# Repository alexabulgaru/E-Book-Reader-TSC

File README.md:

# E-Book-Reader-TSC - Bulgaru Alexandra 331CD

## Diagrama bloc

## Bill Of Materials (BOM)
| Componenta | Achizitie | Datasheet |
| ---------- | --------- | --------- |
| PFMF.050.1 | [Cumpara](https://ro.mouser.com/ProductDetail/Schurter/PFMF.050.2?qs=1auRipcfynCums5v1iucSA%3D%3D) |  [Datasheet](https://ro.mouser.com/datasheet/2/358/typ_PFMF-1275918.pdf) |
| USB4110-GF-A | [Cumpara](https://ro.mouser.com/ProductDetail/GCT/USB4110-GF-A?qs=KUoIvG%2F9IlYiZvIXQjyJeA%3D%3D) | [Datasheet](https://ro.mouser.com/datasheet/2/837/GCT_USB4110_Product_Drawing___20k_cycles-3455479.pdf) |
| USBLC6-2SC6Y | [Cumpara](https://ro.mouser.com/ProductDetail/STMicroelectronics/USBLC6-2SC6Y?qs=gNDSiZmRJS%2FOgDexvXkdow%3D%3D) | [Datasheet](https://ro.mouser.com/datasheet/2/389/usblc6_2sc6y-1852505.pdf) |
| SD0805S020S1R0 | [Cumpara](https://ro.mouser.com/ProductDetail/KYOCERA-AVX/SD0805S020S1R0?qs=jCA%252BPfw4LHbpkAoSnwrdjw%3D%3D) | [Datasheet](https://ro.mouser.com/datasheet/2/40/schottky-3165252.pdf) |
| DMG2305UX-7 | [Cumpara](https://ro.mouser.com/ProductDetail/Diodes-Incorporated/DMG2305UX-7?qs=L1DZKBg7t5F%2FNBHrjfxC%252Bg%3D%3D) | [Datasheet](https://www.diodes.com/assets/Datasheets/DMG2305UX.pdf) |
| XC6220A331MR-G | [Cumpara](https://ro.mouser.com/ProductDetail/Torex-Semiconductor/XC6220A331MR-G?qs=AsjdqWjXhJ8ZSWznL1J0gg%3D%3D) | [Datasheet](https://ro.mouser.com/datasheet/2/760/xc6220-3371556.pdf) |
| Condensator 100 uF TANT | [Cumpara](https://ro.mouser.com/ProductDetail/KYOCERA-AVX/TAJW107M010RNJ?qs=Wtp%252Bf%2FAeVqIH8v1VxV%252B1Rg%3D%3D) | [Datasheet](https://ro.mouser.com/datasheet/2/40/TAJ-3165264.pdf) |
| 112A-TAAR-R03_ATTEND | [Cumpara](https://www.digikey.ro/en/products/detail/attend-technology/112A-TAAR-R03/17633923) | [Datasheet](https://www.attend.com.tw/data/download/file/112A-TAAR-R03_Spec.pdf)
| ESP32-C6-WROOM-1-N8 | [Cumpara](https://ro.mouser.com/ProductDetail/Espressif-Systems/ESP32-C6-WROOM-1-N8?qs=8Wlm6%252BaMh8ST02Gmwp74cw%3D%3D) | [Datasheet](https://ro.mouser.com/datasheet/2/891/Espressif_ESP32_C6_WROOM_1__Datasheet_V0_1_PRELIMI-3239987.pdf) |
| MCP73831 | [Cumpara](https://ro.mouser.com/ProductDetail/Microchip-Technology/MCP73831T-2ACI-OT?qs=yUQqVecv4qvbBQBGbHx0Mw%3D%3D) | [Datasheet](https://ro.mouser.com/datasheet/2/268/MCP73831_Family_Data_Sheet_DS20001984H-3441711.pdf) |
| CHG_LED | [Cumpara](https://store.comet.srl.ro/Catalogue/Product/40478/) | [Datasheet](https://www.snapeda.com/parts/KP-1608SURCK/Kingbright/datasheet/) |
| SI1308EDL-T1-GE3 | [Cumpara](https://ro.mouser.com/ProductDetail/Vishay-Semiconductors/SI1308EDL-T1-GE3?qs=bX1%252BNvsK%2FBramh9tgpOaEw%3D%3D) | [Datasheet](https://www.vishay.com/doc?63399) |
| MBR0530 | [Cumpara](https://ro.mouser.com/ProductDetail/Micro-Commercial-Components-MCC/MBR0530-T?qs=9VyI4qLX4NTSXkb9ynzJnA%3D%3D) | [Datasheet](https://ro.mouser.com/datasheet/2/258/mcc_mbr0520~mbr0560sod123-1179695.pdf) |
| Bobina | [Cumpara](https://ro.mouser.com/ProductDetail/Wurth-Elektronik/744043680?qs=PGXP4M47uW6VkZq%252BkzjrHA%3D%3D) | [Datasheet](https://www.we-online.com/components/products/datasheet/744043680.pdf) |
| FH34SRJ-24S-0.5SH_99_ | [Cumpara](https://ro.mouser.com/ProductDetail/Hirose-Connector/FH34SRJ-24S-0.5SH99?qs=vcbW%252B4%252BSTIpKBl5ap9J8Fw%3D%3D) | [Datasheet](https://ro.mouser.com/datasheet/2/185/FH34SRJ_24S_0_5SH_99__CL0580_1255_6_99_2DDrawing_0-1615044.pdf) |
| BME688 | [Cumpara](https://ro.mouser.com/ProductDetail/Bosch-Sensortec/BME688?qs=IS%252B4QmGtzzqQoVDscqwx3A%3D%3D) | [Datasheet](https://ro.mouser.com/datasheet/2/783/bst_bme688_fl000-2307034.pdf) |
| BD5229G-TR | [Cumpara](https://ro.mouser.com/ProductDetail/ROHM-Semiconductor/BD5229G-TR?qs=4kLU8WoGk0vvnhrrYwdszw%3D%3D) | [Datasheet](https://fscdn.rohm.com/en/products/databook/datasheet/ic/power/voltage_detector/bd52xxg-e.pdf) |
| Buton adaptat | [Cumpara](https://ro.mouser.com/ProductDetail/CK/KMR221GULCLFS?qs=u2NJ%252B70r0goBXaNk7IrU0Q%3D%3D) | [Datasheet](https://www.ckswitches.com/media/1479/kmr2.pdf) |
| MAX17048G+T10 | [Cumpara](https://ro.mouser.com/ProductDetail/Analog-Devices-Maxim-Integrated/MAX17048G%2bT10?qs=D7PJwyCwLAoGnnn8jEPRBQ%3D%3D) | [Datasheet](https://ro.mouser.com/datasheet/2/609/MAX17048_MAX17049-3469099.pdf) |
| W25Q512JVEIQ | [Cumpara](https://ro.mouser.com/ProductDetail/Winbond/W25Q512JVEIQ?qs=l7cgNqFNU1jw6svr3at6tA%3D%3D) | [Datasheet](https://ro.mouser.com/datasheet/2/949/Winbond_W25Q512JV_Datasheet-3240039.pdf) |
| PGB1010603MR | [Cumpara](https://ro.mouser.com/ProductDetail/Littelfuse/PGB1010603MRHF?qs=KvZd0dN2Zg%2FuIq6icj%252BGKA%3D%3D) | [Datasheet](https://www.littelfuse.com/media?resourcetype=datasheets&itemid=8a337998-d54d-466b-be4e-dc5bcd1f9321&filename=littelfuse_pulseguard_pgb1_datasheet.pdf) |
| QWIIC_RIGHT_ANGLE | [Cumpara](https://ro.mouser.com/ProductDetail/GCT/USB4110-GF-A?qs=KUoIvG%2F9IlYiZvIXQjyJeA%3D%3D) | [Datasheet](https://ro.mouser.com/datasheet/2/837/GCT_USB4110_Product_Drawing___20k_cycles-3455479.pdf) |
| DS3231SN# | [Cumpara](https://ro.mouser.com/ProductDetail/Analog-Devices-Maxim-Integrated/DS3231SN?qs=ffX8NcjNb2RmKAb9wAk9Ug%3D%3D) | [Datasheet](https://ro.mouser.com/datasheet/2/609/DS3231-3421123.pdf) |
| CPH3225A C10_SUPERCAP | [Cumpara](https://ro.mouser.com/ProductDetail/Seiko-Semiconductors/CPH3225A?qs=3etwrb1wR%252BhUOph6lAO7eg%3D%3D) | [Datasheet](https://ro.mouser.com/datasheet/2/360/Seiko_Instruments_MicroBattery_E_20230330_2024Jan_-3561061.pdf) |
| Condensator 100nF | [Cumpara](https://ro.mouser.com/ProductDetail/KYOCERA-AVX/06033G104ZAT2A?qs=NXubJDmysXJMPmHfVo6Z%252BA%3D%3D) | [Datasheet](https://ro.mouser.com/datasheet/2/40/KGM_Y5V-3223189.pdf) |
| Condensator 4.7uF | [Cumpara](https://ro.mouser.com/ProductDetail/KYOCERA-AVX/0402ZD475MAT2A?qs=NBFAU1oqP4W4U2PCPHI0sg%3D%3D) | [Datasheet](https://ro.mouser.com/datasheet/2/40/cx5r_KGM-3223198.pdf) |
| Condensator 10uF | [Cumpara](https://ro.mouser.com/ProductDetail/Samsung-Electro-Mechanics/CL10A106KQ8NNNL?qs=xZ%2FP%252Ba9zWqaes9JKSsob2Q%3D%3D) | [Datasheet](https://ro.mouser.com/datasheet/2/585/MLCC-1837944.pdf) |
| Condensator 1uF/50V | [Cumpara](https://ro.mouser.com/ProductDetail/KYOCERA-AVX/06035D105MAT2A?qs=k4kUdCzLgS5%252BURKe1SOIeQ%3D%3D) | [Datasheet](https://ro.mouser.com/datasheet/2/40/cx5r_KGM-3223198.pdf) |
| Rezistenta 10K | [Cumpara](https://ro.mouser.com/ProductDetail/Vishay-Beyschlag/MCS0402MD1002BE000?qs=17u8i%2FzlE8%2F9BrAaXkMk1w%3D%3D) | [Datasheet](https://www.vishay.com/doc?28952) |
| Rezistenta 200 | [Cumpara](https://ro.mouser.com/ProductDetail/Vishay-Beyschlag/MCS0402MD2000BE100?qs=3SvaY9RawMJNVte4F12%252BZQ%3D%3D) | [Datasheet](https://www.vishay.com/doc?28952) |
| Rezistenta 100K | [Cumpara](https://ro.mouser.com/ProductDetail/Vishay-Beyschlag/MCT0603PD1003DP500?qs=5aG0NVq1C4wWAn8Ei3OpZA%3D%3D) | [Datasheet](https://www.vishay.com/doc?28916) |
| Rezistenta 2.2 | [Cumpara](https://ro.mouser.com/ProductDetail/SEI-Stackpole/RMCF0402FT2R20?qs=IPgv5n7u5QbBgyl0jwhwsA%3D%3D) | [Datasheet](https://ro.mouser.com/datasheet/2/385/SEI_RMCF_RMCP-3077565.pdf) |
| Rezistenta 5K1| [Cumpara](https://www.venkel.com/part/TFCR0603-16W-K-5690FT) | [Datasheet](https://data.venkel.com/documents/tfcr-series?_gl=1*tdo8m*_ga*NTA1MTc5MTcyLjE3NDM4OTMzNjc.*_ga_JRKGBZNVM8*MTc0Mzg5MzM2Ni4xLjAuMTc0Mzg5MzM2OC41OC4wLjA.) |
| Rezistenta 2K | [Cumpara](https://ro.mouser.com/ProductDetail/Vishay-Beyschlag/MCS04020C2001FE000?qs=wTZ%2FFzl837YG0wIkZJJOwQ%3D%3D) | [Datasheet](https://www.vishay.com/doc?28705) |
| Rezistenta 0.47 | [Cumpara](https://ro.mouser.com/ProductDetail/SEI-Stackpole/CSR0402JKR470?qs=IPgv5n7u5QawIB6nBEt8wA%3D%3D) | [Datasheet](https://ro.mouser.com/datasheet/2/385/SEI_CSR_CSRN-3077593.pdf) |
| Rezistenta 15 | [Cumpara](https://ro.mouser.com/ProductDetail/YAGEO/RT0402FRE0715RL?qs=BXCcY9r%252B08DFFpLSkPOIqQ%3D%3D) | [Datasheet](https://ro.mouser.com/datasheet/2/447/PYu_RT_1_to_0_01_RoHS_L_15-3461507.pdf) |
| SJ | [Cumpara](https://grabcad.com/library/solder-jumpers-1) | [Datasheet](https://docs.rs-online.com/6fae/A700000010766261.pdf)

## Functionalitatea Hardware
#### Alimentare & Baterie:
USB-C furnizeaza 5 V, intra in controllerul de incarcare Li-Po si LDO-ul de 3.3 V. Acest 3.3 V alimenteaza microcontrolerul (ESP32-C6), senzorii si perifericele. Bateria Li-Po asigura functionarea cand nu este disponibila o sursa USB.

Microcontrolerul (ESP32-C6) ruleaza firmware-ul, se conecteaza la retea (Wi-Fi 6, BLE), citeste senzorii interni (BME688, DS3231) si scrie/afiseaza pe ecranul E-Paper. Poate salva date sau citi fisiere din memoria externa Flash NOR sau de pe cardul SD.

#### Senzori & RTC:
BME688 (temperatura, umiditate, presiune, compusi volatili) si DS3231 (timp real) sunt pe magistrala I2C, astfel incat datele sunt preluate usor si prelucrate.

#### Afisaj E-Paper:
Se actualizeaza prin magistrala SPI; microcontrolerul trimite datele necesare prin pinul EPD_CS (chip select), EPD_DC (command/data), EPD_RST, iar afisajul confirma starea prin EPD_BUSY.

#### Extensii:
Qwiic / Stemma QT ofera posibilitatea de a conecta senzori suplimentari pe magistrala I2C; exista si un slot SD.

## Pini ESP32-C6
| Nume      | GPIO / Pin       | Functie                                         | Descriere                                                                                                                    |
|-----------------|------------------|-------------------------------------------------|------------------------------------------------------------------------------------------------------------------------------|
| **3V3**         | 3V3             | Sursa principala de 3.3V                        | Asigura alimentarea necesara functionarii ESP32-C6 si a componentelor logice de pe placa                                     |
| **EN (Reset)**  | EN              | Activare/Dezactivare microcontroler             | Controleaza alimentarea interna a modulului ESP32-C6; un impuls LOW poate reseta intregul sistem                             |
| **USB_D-**      | IO12            | Linia negativa pentru USB                       | Utilizata in transferul de date prin protocol USB 2.0, in pereche diferentiala cu USB_D+                                     |
| **USB_D+**      | IO13            | Linia pozitiva pentru USB                       | Utilizata in transferul de date prin protocol USB 2.0, in pereche diferentiala cu USB_D-                                     |
| **Buton Boot**  | IO9             | Intrare in modul bootloader                     | Se conecteaza la masa pentru a forta incarcarea bootloader-ului ESP32-C6 (flash/programare firmware)                         |
| **Buton Change**| IO15            | Comutare mod de operare                         | Poate fi configurat in firmware pentru a schimba starea aplicatiei sau diverse moduri de functionare                        |
| **TX (UART)**   | TXD0 / GPIO16   | Emisie seriala (UART)                           | Trimite date catre un terminal serial sau adaptor USB-serial, folosit pentru debug sau comunicatie                          |
| **RX (UART)**   | RXD0 / GPIO17   | Receptie seriala (UART)                         | Primeste date de la un terminal serial sau adaptor USB-serial, folosit pentru debug sau comunicatie                         |
| **SCK (SPI)**   | IO6             | Ceas SPI pentru transfer de date                | Genereaza impulsurile de sincronizare pentru toate dispozitivele conectate la magistrala SPI                                 |
| **MOSI (SPI)**  | IO7             | Linie de date catre dispozitive SPI (Master Out)| Transmite informatii de la microcontroler catre NOR Flash, card SD si ecran E-Paper                                          |
| **MISO (SPI)**  | IO2             | Linie de date de la dispozitive SPI (Master In) | Receptioneaza informatii de la card SD, E-Paper si alte periferice SPI                                                      |
| **FLASH_CS**    | IO11            | Selectare chip pentru memoria NOR Flash         | Activeaza NOR Flash atunci cand se lucreaza cu acesta pe magistrala SPI                                                      |
| **EPD_CS**      | IO10            | Selectare chip pentru E-Paper                   | Activeaza modulul E-Paper pe magistrala SPI in timpul transferului de date                                                  |
| **EPD_DC**      | IO5             | Diferentiere comanda/date pentru E-Paper        | Indica daca informatia transmisa pe SPI reprezinta instructiuni de control sau date de afisare                              |
| **EPD_RST**     | IO23            | Reset extern E-Paper                            | Permite repornirea hardware a modulului E-Paper in cazul in care este necesar                                               |
| **EPD_BUSY**    | IO3             | Semnal de ocupare E-Paper                       | Avertizeaza microcontrolerul ca E-Paper este in curs de actualizare si nu poate primi alte comenzi                          |
| **SDA (I2C)**   | IO21            | Linie de date I2C                               | Utilizata pentru comunicatia bidirectionala cu RTC DS3231, senzor BME688 si conector Qwiic/Stemma QT                        |
| **SCL (I2C)**   | IO22            | Linie de ceas I2C                               | Sincronizeaza toate transferurile de pe magistrala I2C, inclusiv cu RTC, senzori si module de extensie                     |
| **SS_SD**       | IO4             | Chip Select pentru card SD (SPI)               | Stabileste cand cardul SD este activ pe magistrala SPI, prevenind conflicte cu alte dispozitive                            |
| **I2C_PW**      | IO19            | Control alimentare senzori I2C                 | Poate porni sau opri tensiunea pentru senzorii conectati la magistrala I2C, contribuind la economisirea energiei           |
| **EPD_3V3_C**   | IO20            | Alimentare 3.3V dedicata E-Paper               | Linie separata de 3.3V pentru a alimenta in mod specific modulul E-Paper si pentru a asigura stabilitatea semnalelor       |
| **32KHZ**       | IO1             | Linie semnal 32 kHz                            | Frecventa de ceas folosita de modulul RTC sau alte circuite care necesita un clock de 32 kHz                                |
| **INT_RTC**     | IO0             | Intrerupere de la RTC DS3231                   | Poate trezi ESP32-C6 din mod sleep sau poate semnala evenimente programate in RTC                                           |
| **RTC_RST**     | IO18            | Reset extern RTC                                | Linie pentru resetarea manuala a ceasului de timp real in situatii speciale                                                |

## Estimare consum

| Componenta       | Consum Activ (aprox) | Consum Sleep (aprox) | Observatii                                                                              |
|------------------|-----------------------|-----------------------|-----------------------------------------------------------------------------------------|
| ESP32-C6         | ~80–100 mA (Wi-Fi)   | ~10–20 µA (DeepSleep)| Principalul consumator; Wi-Fi creste semnificativ consumul in mod activ                 |
| Senzor BME688    | ~2 mA in masurare    | <1 µA in standby     | Majoritatea timpului poate fi oprit sau in standby                                     |
| RTC DS3231       | ~150–200 µA          | ~3 µA in mod backup  | Funcioneaza permanent, dar consuma relativ putin                                        |
| NOR Flash (SPI)  | ~10–30 mA            | ~1 µA (Deep PwrDown) | Activ doar la operatiile de citire/scriere                                             |
| E-Paper Display  | ~20–50 mA la refresh | ~0 µA in pasiv       | Odata afisat, nu mai consuma energie pentru mentinerea imaginii                        |
| LDO + pasive     | ~10–50 µA            | n/a                  | Curent de repaus al regulatorului si mici consumuri auxiliare (rezistente, LED-uri etc.) |

## Etape implementare
1. Schematic: Am creat schematicul pe baza schemei electrice furnizate. Am folosit biblioteca DeskAssitant si am rulat ERC pentru a verifica prezenta erorilor.

2. PCB:
- Din schematic am dat "switch to PCB" si am plasat componentele conform modelului. Am desenat placa potrivit dimensiunilor, adaugand si decuparile. Componentele principale erau destul de vizibile, condensatoarele si rezistenele le-am asezat in functie de proximitatea acestora din schematic fata de componentele mari.
-Am facut autorutare pe top si pe bottom cu 0.15 mm, apoi am modificat grosimile firelor de alimentare sa fie minim 0.30 mm.
- Am creat planurile de masa cu semnalul GND, ulterior adaugand si via stitching tot cu semnalul GND. Majoritatea via stitching-urilor le-am pozitionat in jurul antenei.

3. 3D: Am adaugat in schematic componentele 3D din [Component Search Engine](https://componentsearchengine.com). Le-am pozitionat apoi conform footprint-ului.

4. Update carcasa: Dupa ce am pozitionat placuta in carcasa, am modificat carcasa astfel incat sa se potriveasca mufele.

5. Am creat modelele 3D pentru carcasa si display conform schemelor si le-am asezat in carcasa.

## Erori/probleme intampinate
1. Am acceptat erorile de PCB de tipul SMD-Hole Board.

2. Am uitat sa verific schematicul cu ERC prima data si am rulat abia dupa ce am terminat de importat toate componentele 3D. Am observat o eroare, a trebuit sa refac o conexiune si am reluat procesul de rutare, planuri de masa si via stitching.

3. Am modificat butoanele sa se potriveasca pe footprint.

4. Cand am generat prima data placuta 3D, aveam o portiune din PCB incompleta pe care nu am vazut-o. Din acest motiv, placuta avea gauri. Am corectat si am facut iar planul de masa si via stitching.

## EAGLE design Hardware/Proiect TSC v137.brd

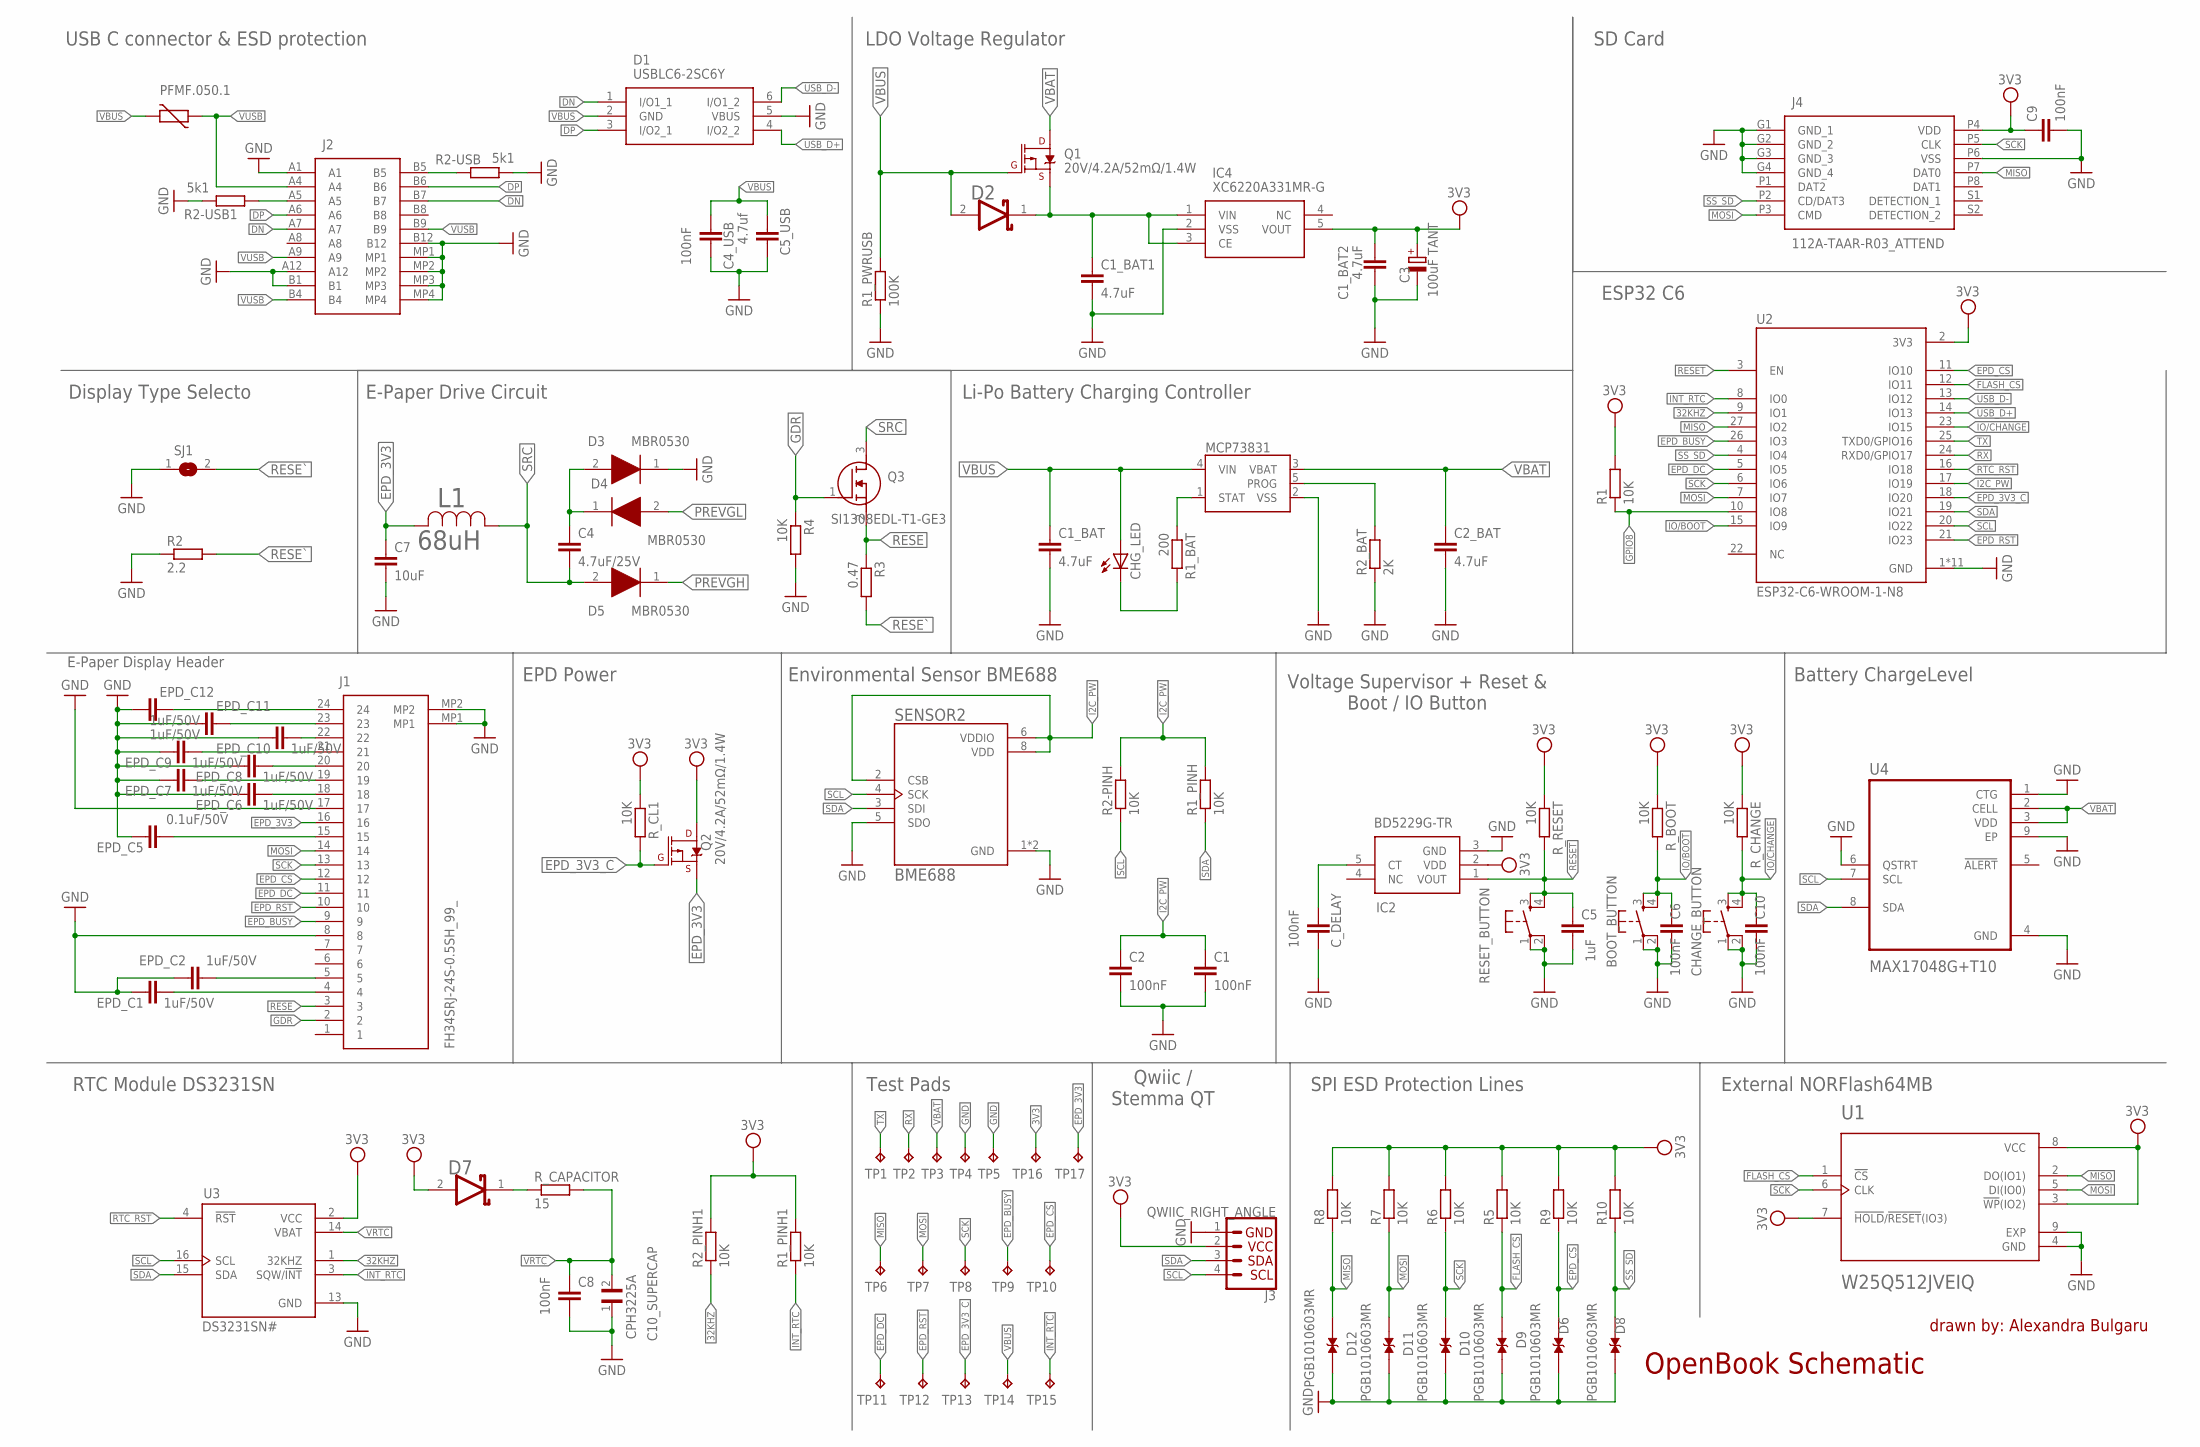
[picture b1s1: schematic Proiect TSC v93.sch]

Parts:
BOOT_BUTTON: BUTTON_CUSYOMV1; MYBUTTON
C1, C2, C4_USB, C6, C8, C10: 100nF; EAGLE-LTSPICE_C0402
C1_BAT, C1_BAT1, C1_BAT2, C2_BAT: 4.7uF; EAGLE-LTSPICE_C0402
C3: 100uF TANT; RCL_CT3528
C4: 4.7uF/25V; EAGLE-LTSPICE_C0402
C5: 1uF; EAGLE-LTSPICE_C0402
C5_USB: 4.7uf; EAGLE-LTSPICE_C0402
C7: 10uF; EAGLE-LTSPICE_C0402
C9: 100nF; ESP32_WROVER_EAGLE-LTSPICE_C0402
C10_SUPERCAP: CPH3225A; CAPCP3225X100N
CHANGE_BUTTON: BUTTON_CUSYOMV1; MYBUTTON
CHG_LED: ADAFRUIT_LEDCHIP-LED0603; ADAFRUIT_CHIP-LED0603
C_DELAY: 100nF; EAGLE-LTSPICE_C0402
D1: USBLC6-2SC6Y; SOT95P280X145-6N
D2, D7: ESP32_WROVER_AVX---SD0805S020S1R0_AVX_SD0805S020S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; ESP32_WROVER_AVX---SD0805S020S1R0_AVX_SD0805S020S1R0_0
D3, D4, D5: MBR0530; SOD3716X135N
D6, D8, D9, D10, D11, D12: PGB1010603MR; DIOC1608X36N
EPD_C1, EPD_C2, EPD_C6, EPD_C7, EPD_C8, EPD_C9, EPD_C10, EPD_C11, EPD_C12: 1uF/50V; EAGLE-LTSPICE_C0402
EPD_C5: 0.1uF/50V; EAGLE-LTSPICE_C0402
IC2: BD5229G-TR; SOT95P280X125-5N
IC4: XC6220A331MR-G; SOT95P280X120-5N
J1: FH34SRJ-24S-0.5SH_99_; FH34SRJ24S05SH99
J2: SAMACSYS_PARTS_USB4110-GF-A; SAMACSYS_PARTS_USB4110GFA
J3: QWIIC_RIGHT_ANGLE; JST04_1MM_RA
J4: 112A-TAAR-R03_ATTEND; 112ATAARR03ATTEND
L1: 68uH; IND_4828-WE-TPC_WRE
MCP73831: ESP32_WROVER_SPARKFUN-IC-POWER_MCP73831; ESP32_WROVER_SPARKFUN-IC-POWER_SOT23-5
PFMF.050.1: ESP32C6_VARISTORCN1812; ESP32C6_VARISTOR_CT/CN1812
Q1, Q2: 20V/4.2A/52mΩ/1.4W; ESP32_WROVER_SPARKFUN-DISCRETESEMI_SOT23-3
Q3: SI1308EDL-T1-GE3; SOT65P210X110-3N
R1, R1_PINH, R1_PINH1, R2-PINH, R2_PINH1, R4, R5, R6, R7, R8, R9, R10: 10K; ESP32_WROVER_EAGLE-LTSPICE_R0402
R1_BAT: 200; ESP32_WROVER_EAGLE-LTSPICE_R0402
R1_PWRUSB: 100K; ESP32_WROVER_EAGLE-LTSPICE_R0402
R2: 2.2; ESP32_WROVER_EAGLE-LTSPICE_R0402
R2-USB, R2-USB1: 5k1; ESP32_WROVER_EAGLE-LTSPICE_R0402
R2_BAT: 2K; ESP32_WROVER_EAGLE-LTSPICE_R0402
R3: 0.47; ESP32_WROVER_EAGLE-LTSPICE_R0402
RESET_BUTTON: BUTTON_CUSYOMV1; MYBUTTON
R_BOOT: 10K; ESP32_WROVER_EAGLE-LTSPICE_R0402
R_CAPACITOR: 15; ESP32_WROVER_EAGLE-LTSPICE_R0402
R_CHANGE: 10K; ESP32_WROVER_EAGLE-LTSPICE_R0402
R_CL1: 10K; ESP32_WROVER_EAGLE-LTSPICE_R0402
R_RESET: 10K; ESP32_WROVER_EAGLE-LTSPICE_R0402
SENSOR2: BME688; ESP32_WROVER_BME680_PSON80P300X300X100-8N
SJ1: SJ
TP1, TP2, TP3, TP4, TP5, TP6, TP7, TP8, TP9, TP10, TP11, TP12, TP13, TP14, TP15, TP16, TP17: TPTP20R; TP20R
U1: W25Q512JVEIQ; SON127P600X800X80-9N
U2: ESP32-C6-WROOM-1-N8; XCVR_ESP32-C6-WROOM-1-N8
U3: DS3231SN#; SOIC127P1032X265-16N
U4: MAX17048G+T10; SON50P200X200X80-9N

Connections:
3V3: C1_BAT2.2, C3.+, C9.1, D7.2 (ANODE), IC2.2 (VDD), IC4.5 (VOUT), J3.2, J4.P4 (VDD), Q2.3 (D), R1.2, R1_PINH1.2, R2_PINH1.2, R5.2, R6.2, R7.2, R8.2, R9.2, R10.2, R_BOOT.1, R_CHANGE.1, R_CL1.1, R_RESET.1, TP16.TP, U1.3 (!WP!(IO2)), U1.7 (!HOLD!/!RESET!(IO3)), U1.8 (VCC), U2.2 (3V3), U3.2 (VCC)
32KHZ: R2_PINH1.1, U2.9 (IO1), U3.1 (32KHZ)
DN: D1.1 (I/O1_1), J2.A7, J2.B7
DP: D1.3 (I/O2_1), J2.A6, J2.B6
EPD_3V3: C7.1, J1.16, L1.2, Q2.2 (S), TP17.TP
EPD_3V3_C: Q2.1 (G), R_CL1.2, TP13.TP, U2.18 (IO20)
EPD_BUSY: J1.9, TP9.TP, U2.26 (IO3)
EPD_CS: D6.1, J1.12, R9.1, TP10.TP, U2.11 (IO10)
EPD_DC: J1.11, TP11.TP, U2.5 (IO5)
EPD_RST: J1.10, TP12.TP, U2.21 (IO23)
FLASH_CS: D9.1, R5.1, U1.1 (!CS), U2.12 (IO11)
GDR: J1.2, Q3.1 (G), R4.1
GPIO8: R1.1, U2.10 (IO8)
I2C_PW: C1.1, C2.1, R1_PINH.2, R2-PINH.2, SENSOR2.2 (CSB), SENSOR2.6 (VDDIO), SENSOR2.8 (VDD), U2.17 (IO19)
INT_RTC: R1_PINH1.1, TP15.TP, U2.8 (IO0), U3.3 (SQW/!INT)
IO/BOOT: BOOT_BUTTON.3, BOOT_BUTTON.4, C6.1, R_BOOT.2, U2.15 (IO9)
IO/CHANGE: C10.1, CHANGE_BUTTON.3, CHANGE_BUTTON.4, R_CHANGE.2, U2.23 (IO15)
MISO: D12.1, J4.P7 (DAT0), R8.1, TP6.TP, U1.2 (DO(IO1)), U2.27 (IO2)
MOSI: D11.1, J1.14, J4.P3 (CMD), R7.1, TP7.TP, U1.5 (DI(IO0)), U2.7 (IO7)
unnamed: J2.B5, R2-USB.1
unnamed: J2.A5, R2-USB1.1
unnamed: C1_BAT1.1, D2.1 (CATHODE), IC4.1 (VIN), IC4.3 (CE), Q1.2 (S)
unnamed: MCP73831.1 (STAT), R1_BAT.1
unnamed: C4.1, D3.2 (A), D4.1 (K)
unnamed: CHG_LED.C, R1_BAT.2
unnamed: MCP73831.5 (PROG), R2_BAT.2
unnamed: EPD_C1.2, J1.4
unnamed: EPD_C2.2, J1.5
unnamed: EPD_C5.2, J1.15
unnamed: EPD_C6.2, J1.18
unnamed: EPD_C7.2, J1.19
unnamed: EPD_C8.2, J1.20
unnamed: EPD_C10.2, J1.22
unnamed: C_DELAY.1, IC2.5 (CT)
unnamed: D7.1 (CATHODE), R_CAPACITOR.1
unnamed: EPD_C12.2, J1.24
RESE: J1.3, Q3.2 (S), R3.1
RESET: C5.1, IC2.1 (VOUT), RESET_BUTTON.3, RESET_BUTTON.4, R_RESET.2, U2.3 (EN)
RESE`: R2.2, R3.2, SJ1.2
RTC_RST: U2.16 (IO18), U3.4 (!RST)
RX: TP2.TP, U2.24 (RXD0/GPIO17)
SCK: D10.1, J1.13, J4.P5 (CLK), R6.1, TP8.TP, U1.6 (CLK), U2.6 (IO6)
SCL: J3.4, R2-PINH.1, SENSOR2.4 (SCK), U2.20 (IO22), U3.16 (SCL), U4.7 (SCL)
SDA: J3.3, R1_PINH.1, SENSOR2.3 (SDI), U2.19 (IO21), U3.15 (SDA), U4.8 (SDA)
SRC: C4.2, D5.2 (A), L1.1, Q3.3 (D)
SS_SD: D8.1, J4.P2 (CD/DAT3), R10.1, U2.4 (IO4)
TX: TP1.TP, U2.25 (TXD0/GPIO16)
USB_D+: D1.4 (I/O2_2), U2.14 (IO13)
USB_D-: D1.6 (I/O1_2), U2.13 (IO12)
VBAT: C2_BAT.1, MCP73831.3 (VBAT), Q1.3 (D), TP3.TP, U4.2 (CELL), U4.3 (VDD)
VBUS: C1_BAT.1, C4_USB.1, C5_USB.1, CHG_LED.A, D1.2 (GND), D2.2 (ANODE), MCP73831.4 (VIN), PFMF.050.1.2, Q1.1 (G), R1_PWRUSB.2, TP14.TP
VRTC: C8.1, C10_SUPERCAP.2, R_CAPACITOR.2, U3.14 (VBAT)
VUSB: J2.A4, J2.A9, J2.B4, J2.B9, PFMF.050.1.1

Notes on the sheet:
USB C connector & ESD protection
LDO Voltage Regulator
SD Card
ESP32 C6
Li-Po Battery Charging Controller
E-Paper Drive Circuit
Display Type Selecto
E-Paper Display Header
EPD Power
Environmental Sensor BME688
Voltage Supervisor + Reset & Boot / IO Button
Battery ChargeLevel
RTC Module DS3231SN
Test Pads
Qwiic / Stemma QT
SPI ESD Protection Lines
External NORFlash64MB
OpenBook Schematic
drawn by: Alexandra Bulgaru

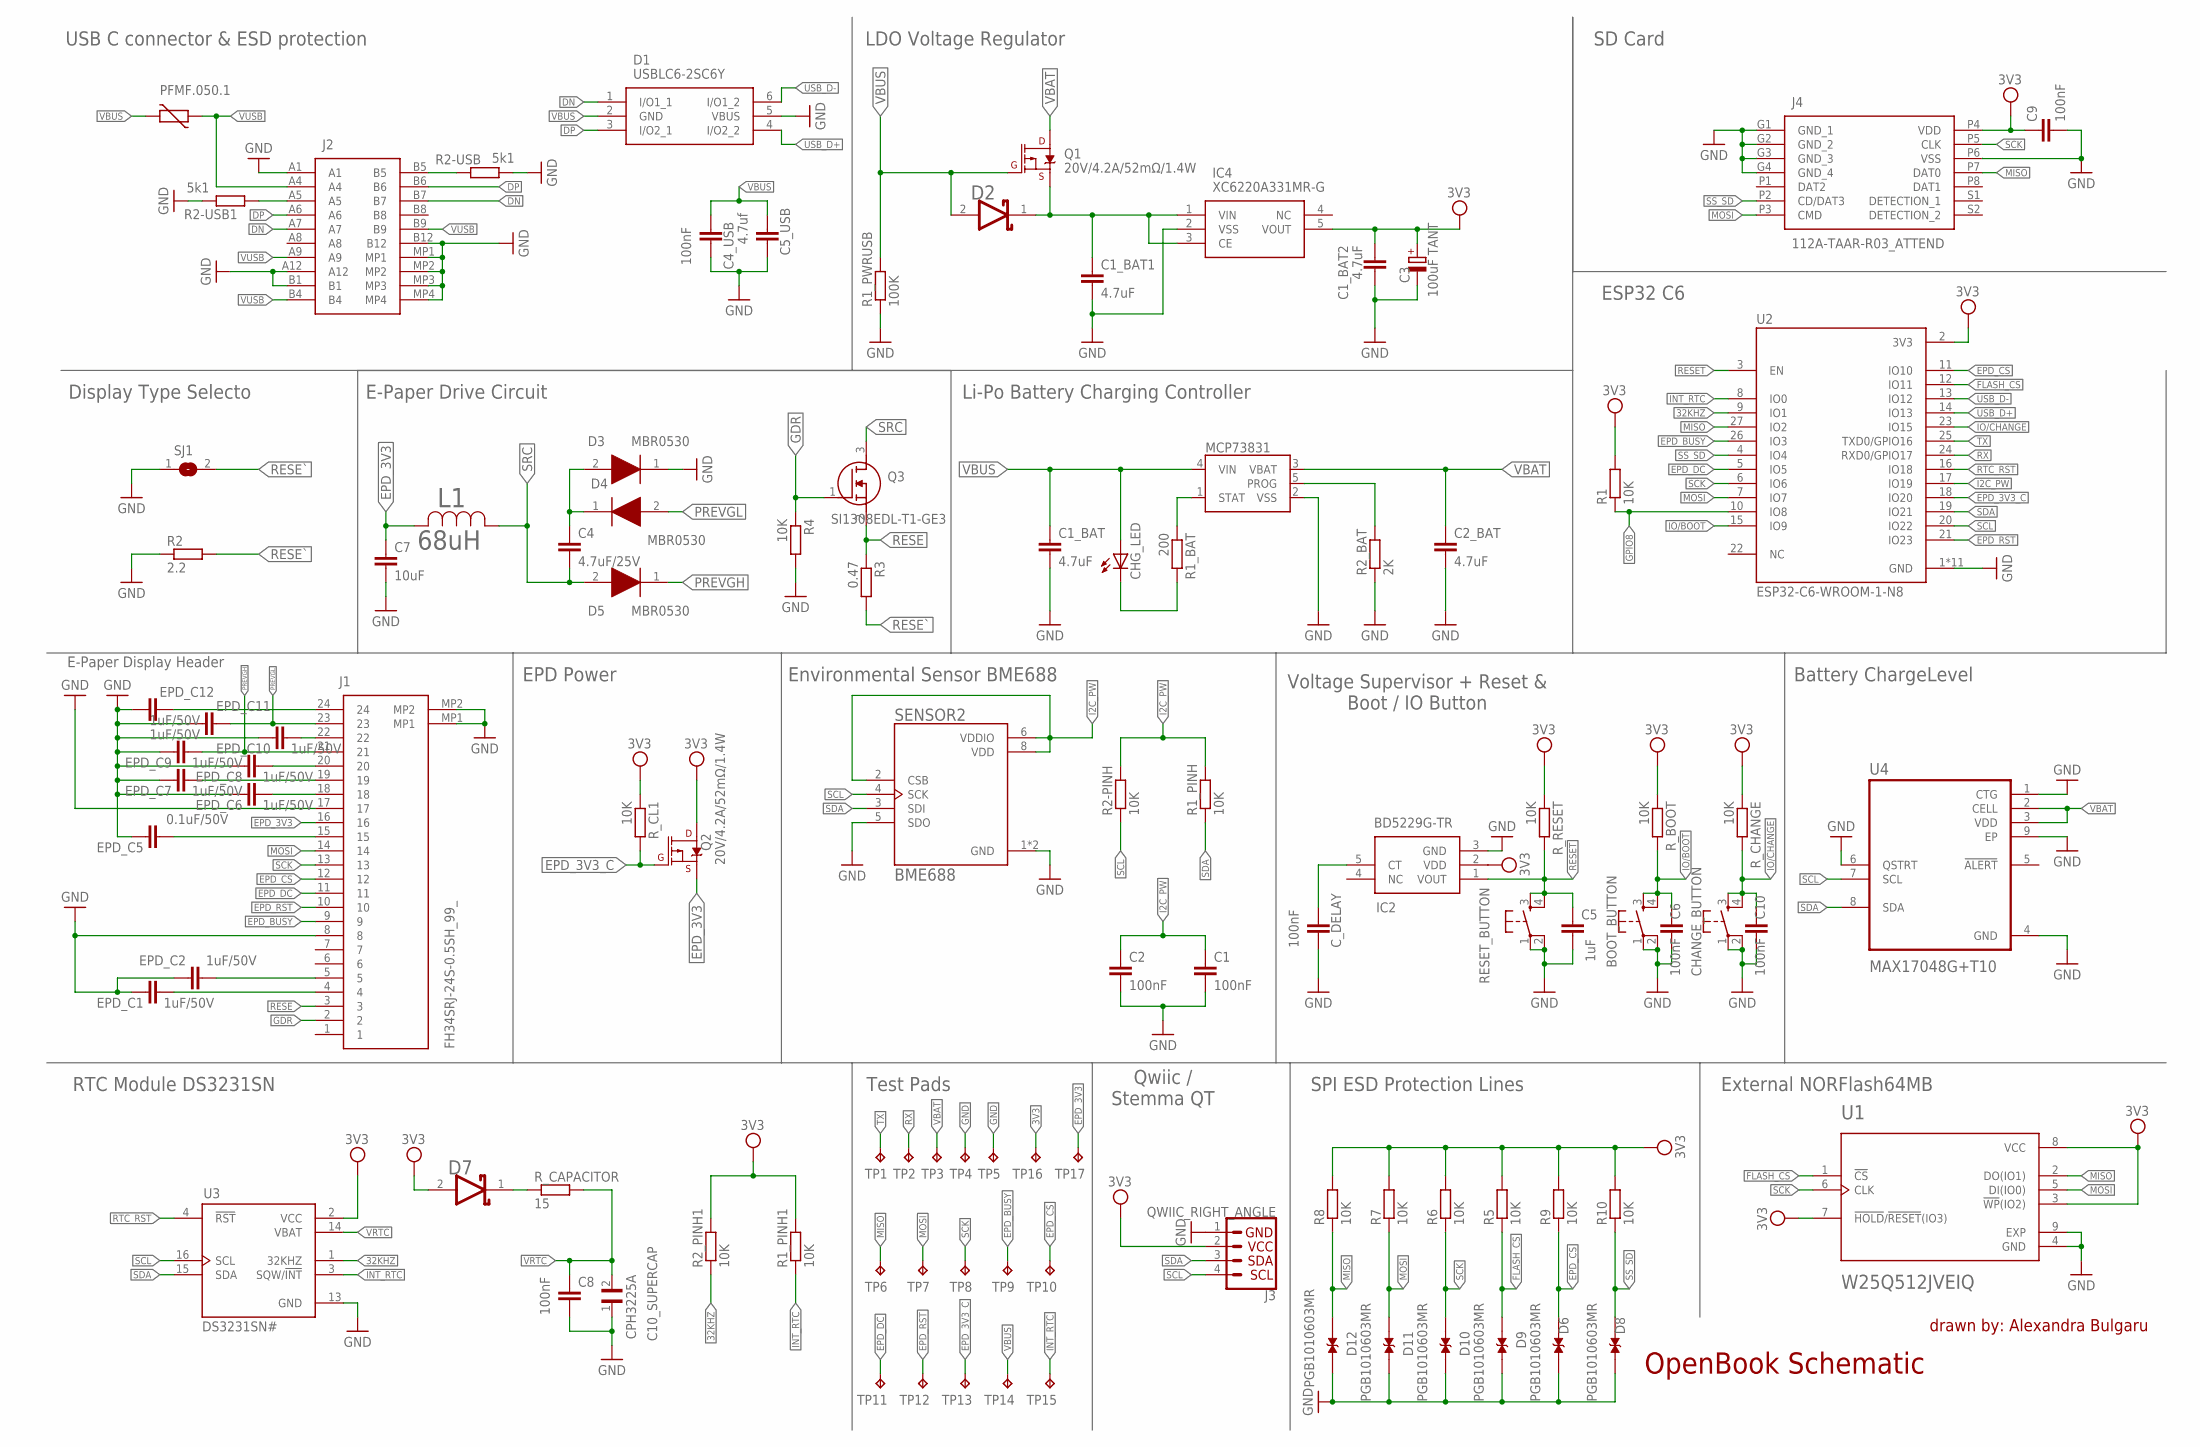
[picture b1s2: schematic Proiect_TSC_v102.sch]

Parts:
BOOT_BUTTON: BUTTON_CUSYOMV1; MYBUTTON
C1, C2, C4_USB, C6, C8, C10: 100nF; EAGLE-LTSPICE_C0402
C1_BAT, C1_BAT1, C1_BAT2, C2_BAT: 4.7uF; EAGLE-LTSPICE_C0402
C3: 100uF TANT; RCL_CT3528
C4: 4.7uF/25V; EAGLE-LTSPICE_C0402
C5: 1uF; EAGLE-LTSPICE_C0402
C5_USB: 4.7uf; EAGLE-LTSPICE_C0402
C7: 10uF; EAGLE-LTSPICE_C0402
C9: 100nF; ESP32_WROVER_EAGLE-LTSPICE_C0402
C10_SUPERCAP: CPH3225A; CAPCP3225X100N
CHANGE_BUTTON: BUTTON_CUSYOMV1; MYBUTTON
CHG_LED: ADAFRUIT_LEDCHIP-LED0603; ADAFRUIT_CHIP-LED0603
C_DELAY: 100nF; EAGLE-LTSPICE_C0402
D1: USBLC6-2SC6Y; SOT95P280X145-6N
D2, D7: ESP32_WROVER_AVX---SD0805S020S1R0_AVX_SD0805S020S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; ESP32_WROVER_AVX---SD0805S020S1R0_AVX_SD0805S020S1R0_0
D3, D4, D5: MBR0530; SOD3716X135N
D6, D8, D9, D10, D11, D12: PGB1010603MR; DIOC1608X36N
EPD_C1, EPD_C2, EPD_C6, EPD_C7, EPD_C8, EPD_C9, EPD_C10, EPD_C11, EPD_C12: 1uF/50V; EAGLE-LTSPICE_C0402
EPD_C5: 0.1uF/50V; EAGLE-LTSPICE_C0402
IC2: BD5229G-TR; SOT95P280X125-5N
IC4: XC6220A331MR-G; SOT95P280X120-5N
J1: FH34SRJ-24S-0.5SH_99_; FH34SRJ24S05SH99
J2: SAMACSYS_PARTS_USB4110-GF-A; SAMACSYS_PARTS_USB4110GFA
J3: QWIIC_RIGHT_ANGLE; JST04_1MM_RA
J4: 112A-TAAR-R03_ATTEND; 112ATAARR03ATTEND
L1: 68uH; IND_4828-WE-TPC_WRE
MCP73831: ESP32_WROVER_SPARKFUN-IC-POWER_MCP73831; ESP32_WROVER_SPARKFUN-IC-POWER_SOT23-5
PFMF.050.1: ESP32C6_VARISTORCN1812; ESP32C6_VARISTOR_CT/CN1812
Q1, Q2: 20V/4.2A/52mΩ/1.4W; ESP32_WROVER_SPARKFUN-DISCRETESEMI_SOT23-3
Q3: SI1308EDL-T1-GE3; SOT65P210X110-3N
R1, R1_PINH, R1_PINH1, R2-PINH, R2_PINH1, R4, R5, R6, R7, R8, R9, R10: 10K; ESP32_WROVER_EAGLE-LTSPICE_R0402
R1_BAT: 200; ESP32_WROVER_EAGLE-LTSPICE_R0402
R1_PWRUSB: 100K; ESP32_WROVER_EAGLE-LTSPICE_R0402
R2: 2.2; ESP32_WROVER_EAGLE-LTSPICE_R0402
R2-USB, R2-USB1: 5k1; ESP32_WROVER_EAGLE-LTSPICE_R0402
R2_BAT: 2K; ESP32_WROVER_EAGLE-LTSPICE_R0402
R3: 0.47; ESP32_WROVER_EAGLE-LTSPICE_R0402
RESET_BUTTON: BUTTON_CUSYOMV1; MYBUTTON
R_BOOT: 10K; ESP32_WROVER_EAGLE-LTSPICE_R0402
R_CAPACITOR: 15; ESP32_WROVER_EAGLE-LTSPICE_R0402
R_CHANGE: 10K; ESP32_WROVER_EAGLE-LTSPICE_R0402
R_CL1: 10K; ESP32_WROVER_EAGLE-LTSPICE_R0402
R_RESET: 10K; ESP32_WROVER_EAGLE-LTSPICE_R0402
SENSOR2: BME688; ESP32_WROVER_BME680_PSON80P300X300X100-8N
SJ1: SJ
TP1, TP2, TP3, TP4, TP5, TP6, TP7, TP8, TP9, TP10, TP11, TP12, TP13, TP14, TP15, TP16, TP17: TPTP20R; TP20R
U1: W25Q512JVEIQ; SON127P600X800X80-9N
U2: ESP32-C6-WROOM-1-N8; XCVR_ESP32-C6-WROOM-1-N8
U3: DS3231SN#; SOIC127P1032X265-16N
U4: MAX17048G+T10; SON50P200X200X80-9N

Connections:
3V3: C1_BAT2.2, C3.+, C9.1, D7.2 (ANODE), IC2.2 (VDD), IC4.5 (VOUT), J3.2, J4.P4 (VDD), Q2.3 (D), R1.2, R1_PINH1.2, R2_PINH1.2, R5.2, R6.2, R7.2, R8.2, R9.2, R10.2, R_BOOT.1, R_CHANGE.1, R_CL1.1, R_RESET.1, TP16.TP, U1.3 (!WP!(IO2)), U1.7 (!HOLD!/!RESET!(IO3)), U1.8 (VCC), U2.2 (3V3), U3.2 (VCC)
32KHZ: R2_PINH1.1, U2.9 (IO1), U3.1 (32KHZ)
DN: D1.1 (I/O1_1), J2.A7, J2.B7
DP: D1.3 (I/O2_1), J2.A6, J2.B6
EPD_3V3: C7.1, J1.16, L1.2, Q2.2 (S), TP17.TP
EPD_3V3_C: Q2.1 (G), R_CL1.2, TP13.TP, U2.18 (IO20)
EPD_BUSY: J1.9, TP9.TP, U2.26 (IO3)
EPD_CS: D6.1, J1.12, R9.1, TP10.TP, U2.11 (IO10)
EPD_DC: J1.11, TP11.TP, U2.5 (IO5)
EPD_RST: J1.10, TP12.TP, U2.21 (IO23)
FLASH_CS: D9.1, R5.1, U1.1 (!CS), U2.12 (IO11)
GDR: J1.2, Q3.1 (G), R4.1
GPIO8: R1.1, U2.10 (IO8)
I2C_PW: C1.1, C2.1, R1_PINH.2, R2-PINH.2, SENSOR2.2 (CSB), SENSOR2.6 (VDDIO), SENSOR2.8 (VDD), U2.17 (IO19)
INT_RTC: R1_PINH1.1, TP15.TP, U2.8 (IO0), U3.3 (SQW/!INT)
IO/BOOT: BOOT_BUTTON.3, BOOT_BUTTON.4, C6.1, R_BOOT.2, U2.15 (IO9)
IO/CHANGE: C10.1, CHANGE_BUTTON.3, CHANGE_BUTTON.4, R_CHANGE.2, U2.23 (IO15)
MISO: D12.1, J4.P7 (DAT0), R8.1, TP6.TP, U1.2 (DO(IO1)), U2.27 (IO2)
MOSI: D11.1, J1.14, J4.P3 (CMD), R7.1, TP7.TP, U1.5 (DI(IO0)), U2.7 (IO7)
unnamed: J2.B5, R2-USB.1
unnamed: J2.A5, R2-USB1.1
unnamed: C1_BAT1.1, D2.1 (CATHODE), IC4.1 (VIN), IC4.3 (CE), Q1.2 (S)
unnamed: MCP73831.1 (STAT), R1_BAT.1
unnamed: C4.1, D3.2 (A), D4.1 (K)
unnamed: CHG_LED.C, R1_BAT.2
unnamed: MCP73831.5 (PROG), R2_BAT.2
unnamed: EPD_C1.2, J1.4
unnamed: EPD_C2.2, J1.5
unnamed: EPD_C5.2, J1.15
unnamed: EPD_C6.2, J1.18
unnamed: EPD_C7.2, J1.19
unnamed: EPD_C8.2, J1.20
unnamed: EPD_C10.2, J1.22
unnamed: C_DELAY.1, IC2.5 (CT)
unnamed: D7.1 (CATHODE), R_CAPACITOR.1
unnamed: EPD_C12.2, J1.24
RESE: J1.3, Q3.2 (S), R3.1
RESET: C5.1, IC2.1 (VOUT), RESET_BUTTON.3, RESET_BUTTON.4, R_RESET.2, U2.3 (EN)
RESE`: R2.2, R3.2, SJ1.2
RTC_RST: U2.16 (IO18), U3.4 (!RST)
RX: TP2.TP, U2.24 (RXD0/GPIO17)
SCK: D10.1, J1.13, J4.P5 (CLK), R6.1, TP8.TP, U1.6 (CLK), U2.6 (IO6)
SCL: J3.4, R2-PINH.1, SENSOR2.4 (SCK), U2.20 (IO22), U3.16 (SCL), U4.7 (SCL)
SDA: J3.3, R1_PINH.1, SENSOR2.3 (SDI), U2.19 (IO21), U3.15 (SDA), U4.8 (SDA)
SRC: C4.2, D5.2 (A), L1.1, Q3.3 (D)
SS_SD: D8.1, J4.P2 (CD/DAT3), R10.1, U2.4 (IO4)
TX: TP1.TP, U2.25 (TXD0/GPIO16)
USB_D+: D1.4 (I/O2_2), U2.14 (IO13)
USB_D-: D1.6 (I/O1_2), U2.13 (IO12)
VBAT: C2_BAT.1, MCP73831.3 (VBAT), Q1.3 (D), TP3.TP, U4.2 (CELL), U4.3 (VDD)
VBUS: C1_BAT.1, C4_USB.1, C5_USB.1, CHG_LED.A, D1.2 (GND), D2.2 (ANODE), MCP73831.4 (VIN), PFMF.050.1.2, Q1.1 (G), R1_PWRUSB.2, TP14.TP
VRTC: C8.1, C10_SUPERCAP.2, R_CAPACITOR.2, U3.14 (VBAT)
VUSB: J2.A4, J2.A9, J2.B4, J2.B9, PFMF.050.1.1

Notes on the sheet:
USB C connector & ESD protection
LDO Voltage Regulator
SD Card
ESP32 C6
Li-Po Battery Charging Controller
E-Paper Drive Circuit
Display Type Selecto
E-Paper Display Header
EPD Power
Environmental Sensor BME688
Voltage Supervisor + Reset & Boot / IO Button
Battery ChargeLevel
RTC Module DS3231SN
Test Pads
Qwiic / Stemma QT
SPI ESD Protection Lines
External NORFlash64MB
OpenBook Schematic
drawn by: Alexandra Bulgaru

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
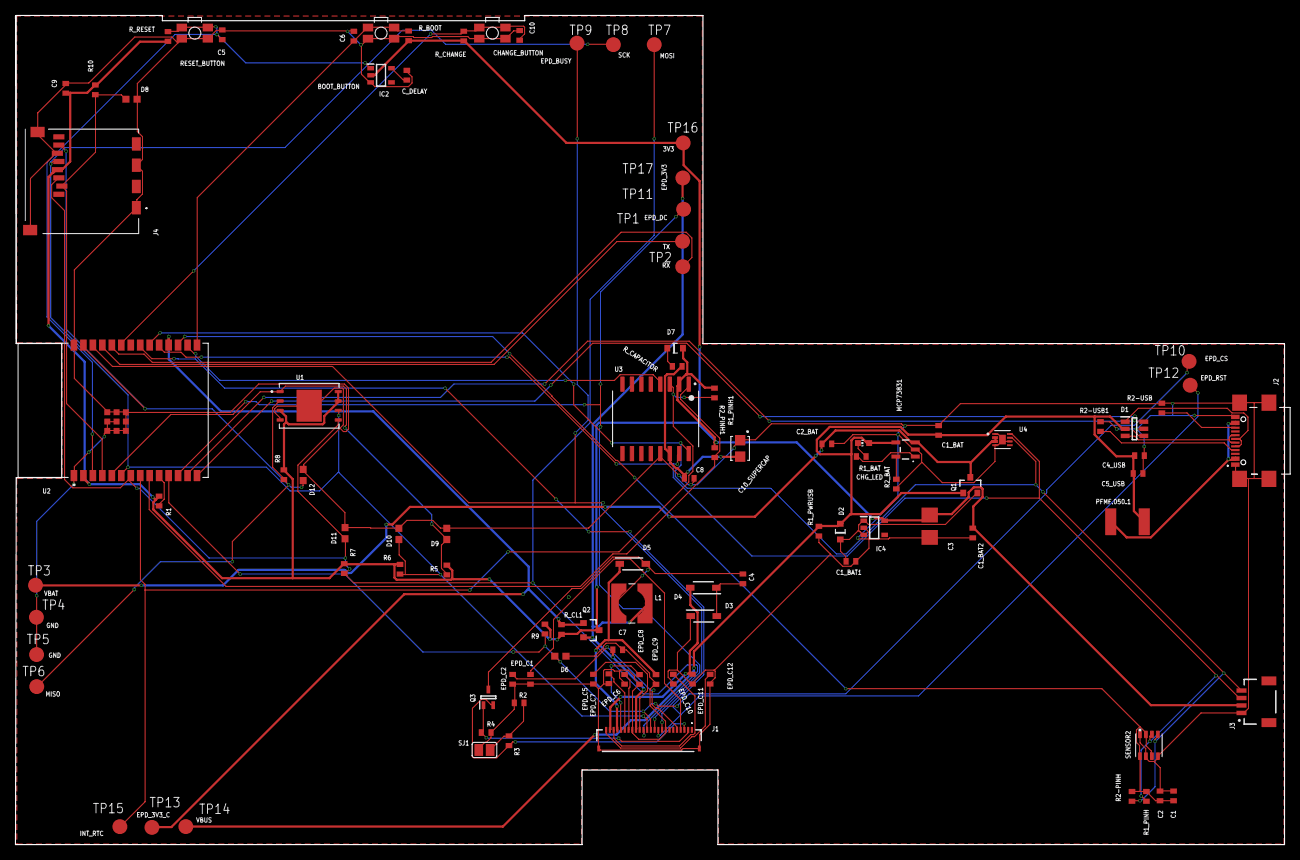
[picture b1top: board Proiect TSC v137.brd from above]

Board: 2 copper layers, 170.2 x 111.2 mm, 103 parts (0 on the bottom side), 56 nets.

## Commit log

2025-04-05 Create LICENSE
2025-04-05 project done
2025-04-06 readme done
2025-04-12 bugs done

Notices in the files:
parts and their libraries:
COPYRIGHT: Copyright (C) 2024 Ultra Librarian. All rights reserved.
